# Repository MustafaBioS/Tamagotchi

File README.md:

# Tamagotchi
A Tamagotchi is a digital pet that you take care of, This project seemed fun to play with and fun to make so i decided to make it!

# How To Recreate
## Components
To make this project you need this list of components:
- XIAO-nRF52840
- 128x32 OLED Display
- Tactile Switches
- Buzzer
- Battery Cell

## Bill Of Materials
| **Item** | **Price** | **Link** |
| --- | --- | --- |
| `XIAO-nRF52840` | $17.00 | [Link](https://www.amazon.com/XIAO-nRF52840-3PCS-Pack-CircuitPython/dp/B09T9VVQG7?th=1&language=en_US&currency=USD) |
| `128x32 OLED Display` | $6.08 | [Link](https://www.amazon.eg/-/en/OLED-0-96-Display-Module-Interface/dp/B0DMQHDK9Y/ref=sr_1_1?crid=1V383W4B7XRQ2&dib=eyJ2IjoiMSJ9.xtNK-FO46kHlX8cL81xleaHLnlXC4bfPEJtGa2VdkjVz65MUDbo6qylT_iDZYEYg1mdmQTvqr4kTnOiR8FPYZ4LBwnERiuWNJJzB58cDYcER26yUjK1peJqLVyuCnMowdg3YHcPgK87Rjz0TyFLcbgLBOh5wuKSambjgAo7EpDiBf9F8bep_nnKO79nEZ-UV0XnGD-ZO-Fg0JfbI_smmnbAyvo3LLmnpZOuWPYfU9AiQosOERxarS1NV7IpR4uAuPhCIICacYEpXvSo3XI0Ze9kmftLGkSXSd_BJrjkc0Ns._gyReaL_mpUuGXTk4_m1MhkrgS7T_JF2KDCv7nuaOkE&dib_tag=se&keywords=128x32+oled+display&qid=1781445359&sprefix=128x32+oled+di%2Caps%2C235&sr=8-1) |
| `Tactile Switches` | $2.62 | [Link](https://www.amazon.eg/20Pcs-Momentary-Tactile-Button-Switch/dp/B0DRGP5733/ref=sr_1_1_sspa?crid=2IQ18AR65TII0&dib=eyJ2IjoiMSJ9._KczJwgVD4c5T3fLctZYd6BY7x3OMpdFpmYrvZTapcNBjkOuzX8CQMWua_Ze9MS19UKl8RX0XlgTrqv53JNogrKhcInM0btarrW-16jTZDp2_wUSNCB_ON6aQPzCxOL0dfczAUkUsZLoaqaxfeqr8_OMUqi6hEvThJqRTRvIOjYUPdl5nHMV1SRGgps9LBO6o-ZaFa952PXL6e2jChaVrbInk1QyTnE08THdKWwRXtwx03Bzp5n7VK3td8b2JYdxs1EXKPWehQjUZZ5BE82-TzmWjsetEqiGIBdvMp0cFlQ.NCMyliC8A-hbQQUaIm2nErRMhmniu91uc_ZrjmG7KL8&dib_tag=se&keywords=tactile+switch&qid=1781445409&sprefix=tactile+switch%2Caps%2C183&sr=8-1-spons&aref=RQGxjAXcU6&sp_csd=d2lkZ2V0TmFtZT1zcF9hdGY&psc=1) |
| `Buzzer` | $1.35 | [Link](https://www.amazon.eg/Generic-Buzzer-12V/dp/B0CTR4D3D8/ref=sr_1_3_sspa?crid=2S8GPSAVCHADG&dib=eyJ2IjoiMSJ9.GwPYCF1zc17ac8eycWyPMEF3Un_ajQwD5sjKKLu3Am5CQ_gBVTRLajpZKlUfODKVrzJj-qYdCdOZINcWmIIolV8oO0tVfo4ANUjGOhx2_q5HPfY2N7lN685v210-g8KP_5NM1OBZcTP-6y2yspTxe-sFJzpGq7550vWisvKCDh7-TeZsugEpMwgjMkCbTam-QJ4zmBi72-zAb8_Z7tQ5mSVaw97bInUBGsXVPJMmgzVZuh1L8iQ1iUtfuBy4NIJEYeyx3en6uiDthCmkc6doR-LIl-9z8jh5FWLyZRhSG4I.6Cmt1wJeu-1gBT5GTEcEJgYaOfVTcyr6Ig_0SSJoygk&dib_tag=se&keywords=buzzer&qid=1781445439&sprefix=buzzer%2Caps%2C205&sr=8-3-spons&aref=AaGWQyJukU&sp_csd=d2lkZ2V0TmFtZT1zcF9hdGY&psc=1) |
| `Battery` | $1.16 | [Link](https://www.amazon.eg/-/en/Camelion-Super-Heavy-Carbon-Batteries/dp/B0CXJGDGF4/ref=sr_1_4?crid=1UD0ST73WHL95&dib=eyJ2IjoiMSJ9.k6im0orxu-MB0ffgZeC9XmejlDjUzQD9mynMhOZhcJTmR7eVImN4Qt0d7G3nx06kf_CDwNei4m-hgi8Ad801SjkaWttEluOy_c_1Viy9o9acG8ucwB3qxelNl2EI9l2DwEy9-6lb93ziDz-83cUn_CB9vFG6Pbm2QG6zZAbE9pkreXjdOm1rbSYlAx_OVHDxmz2HjOcjY3EQrRK9GnCSz3e2AMlAbZx-Fu6OZhabNul-qm5Q72b-epEP-B0a0Yl8zfM5ftJtUIKEBzqwp7MB41Ziqri_dxKp3xsEqrHUJrs.4dIyCAQ33KMNbDifUoAFL55ZA1AELARmvQ9z91sg8F8&dib_tag=se&keywords=Battery+cell&qid=1781445589&sprefix=battery+cel%2Caps%2C179&sr=8-4) |

# PCB, Schematic, and Zine

## [PCB](https://github.com/MustafaBioS/Tamagotchi/blob/main/hardware/Tamagotchi.kicad_pcb)

## [Schematic](https://github.com/MustafaBioS/Tamagotchi/blob/main/hardware/Tamagotchi.kicad_sch)

## [Zine](https://github.com/MustafaBioS/Tamagotchi/blob/main/docs/Zine)

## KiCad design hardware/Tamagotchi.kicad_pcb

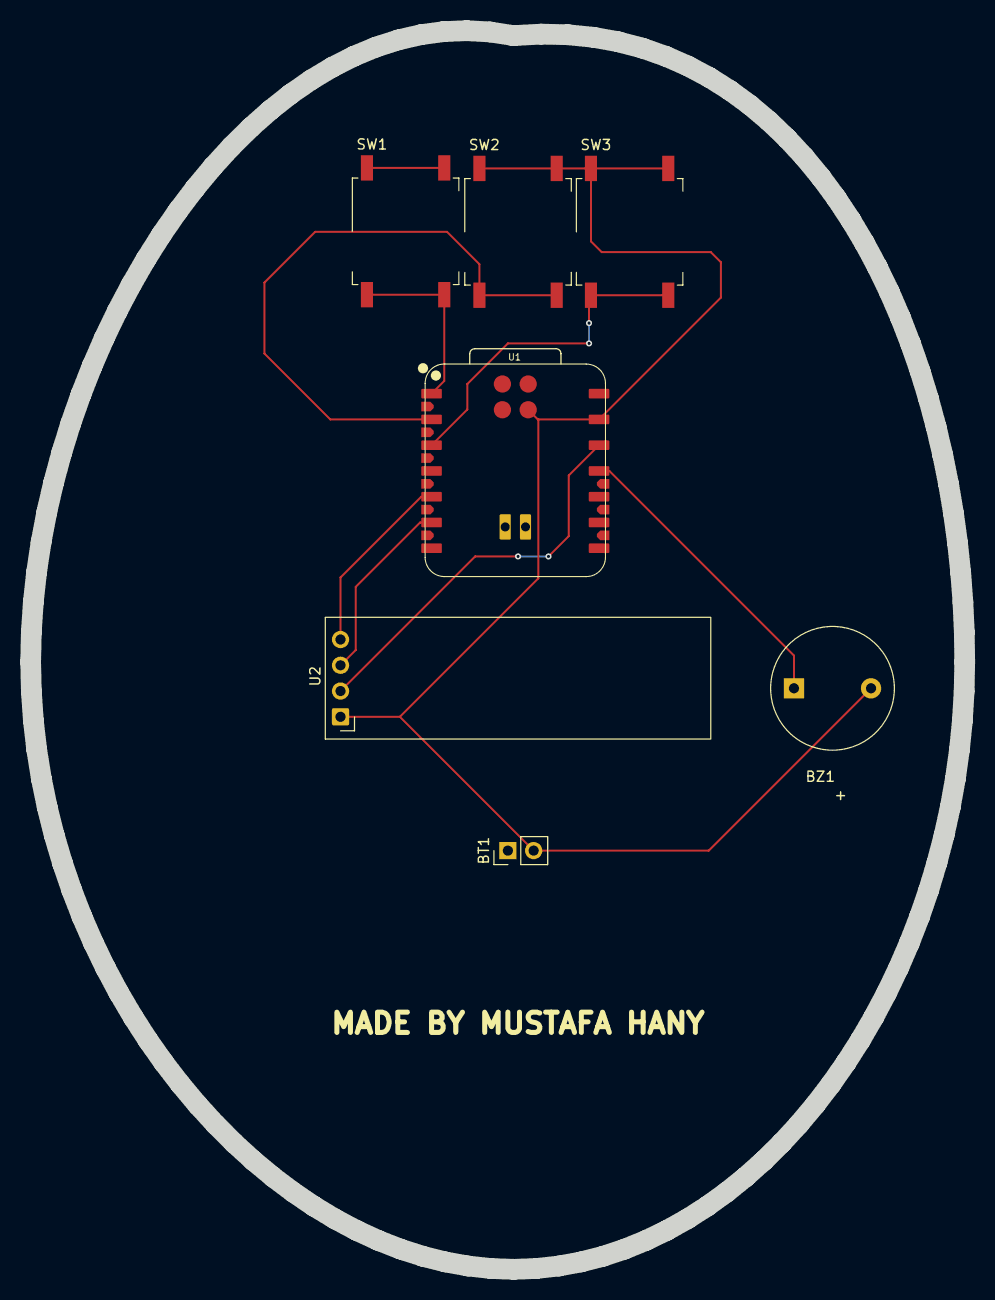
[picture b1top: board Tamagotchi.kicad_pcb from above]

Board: 2 copper layers, 92.1 x 122.1 mm, 7 parts (0 on the bottom side), 8 nets.

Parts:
BT1: Battery_Cell; PinHeader_1x02_P2.54mm_Vertical
BZ1: Buzzer; Buzzer_12x9.5RM7.6
SW1, SW2, SW3: SW_Push; SW_MEC_5GSH9
U1: XIAO-nRF52840-Plus-SMD
U2: ER_OLEDM0.91_1x-I2C

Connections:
GND: BT1.2 (-), BZ1.2 (-), SW2.1, SW3.1, U1.13 (GND), U1.27 (GND), U2.1 (GND)
unnamed: BZ1.1 (+), U1.11 (P1.15_D10_MOSI)
unnamed: U1.12 (3V3), U2.2 (VCC)
unnamed: SW1.2 (2_2), U1.1 (P0.02_A0_D0)
unnamed: SW2.2, U1.2 (P0.03_A1_D1)
unnamed: U1.5 (P0.04_A4_D4_SDA), U2.4 (SDA)
unnamed: U1.6 (P0.05_A5_D5_SCL), U2.3 (SCL)
unnamed: SW3.2, U1.3 (P0.28_A2_D2)

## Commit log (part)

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2026-06-14 Rename BOM.csv to docs/BOM.csv
2026-06-14 Rename Tamagotchi.ino to firmware/Tamagotchi.ino
2026-06-14 Rename Tamagotchi.kicad_pcb to hardware/Tamagotchi.kicad_pcb
2026-06-14 Rename Gerber.zip to hardware/Gerber.zip
2026-06-14 Rename Tamagotchi.kicad_pro to hardware/Tamagotchi.kicad_pro
2026-06-14 Rename Tamagotchi.kicad_sch to hardware/Tamagotchi.kicad_sch
2026-06-14 Rename A5 - 2.png to Zine
2026-06-14 Rename README.md to docs/README.md
2026-06-30 Rename JOURNAL (3).md to JOURNAL.md
